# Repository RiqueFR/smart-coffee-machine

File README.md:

# smart-coffee-machine

Esse projeto consiste na adaptação de uma cafeteira comum, em uma cafeteira smart, usando um microcontrolador ESP32, sensores e conexão com o [Home Assistant](https://www.home-assistant.io/), por meio do sistema [ESPHome](https://esphome.io/),
que permite a automatização dela com outros dispositivos, como por exemplo a Alexa.</br>
É possível assistir a demonstração e explicação do projeto por meio do seguinte vídeo:

Esse projeto usa as ferramentas/plataformas:
- PlatformIO
- Home Assistant
- ESPHome
- Node-RED
- Alexa

## Features

- Escolher a quantidade de café por meio do número de xícaras
- Interface na cafeteira (botões para escolher a quantidade de xícaras, display para exibir a quantidade e o status)
- Conexão com o Home Assistant
- Por meio da conexão com o Home Assistant é possível integrar a cafeteira com diversos outro serviços, como por exemplo comandos de voz da Alexa
- Enchimento automático do reservatório de água da cafeteira
- Sensor para não ser ativada sem uma xícara

## Usage

Para usar esse projeto, você precisa de pelo menos o ESPHome instalado, para que seja possível passar o código para o microcontrolador, basta colocar o projeto na pasta do ESPHome, e usar as ferramentas da plataforma para subir o código.</br>
Existe a versão do código na branch "main" que não necessita do ESPHome, porém ela é desprovida de qualquer conexão com o Home Assistant ou Alexa.</br>

O projeto foi feito com o intuito de ser apresentado na amostra de projetos da disciplina de Projeto Integrado de Computação 2 da UFES, portanto alguns detalhes foram pensados para isso, e caso venha a ser reproduzido para uso pessoal, devem ser abordados outros métodos.</br>
Portanto, até existe um esquemático do projeto na branch "schematic", mas ele deve ser alterado para o seu uso, e apenas usado como base.</br>

O projeto foi calibrado para uso com a cafeteira que tínhamos acesso, portanto ele deve ser recalibrado para outras cafeteiras, isso pode ser feito colocando xícaras de café cheias de água no reservatório da cafeteira e observar as diferenças de distância lidas pelo sensor de ultrassom para cada xícara,
esse valor deve ser setado na variável apropriada.</br>

Para apresentar o projeto na amostra, foi usado uma pequena bomba de água para encher o reservatório, o que não é prático caso o projeto seja feito para uso, o melhor seria usar uma válvula que libera ou bloqueia a passagem de água, e que esteja ligada a tubulação,
para que o enchimento seja feito de maneira totalmente automática.</br>

A branch configs possui configurações das conexões/ferrantas usadas pelo projeto, arquivos de configuração do Home Assistant, Node-RED e ESPHome. Os arquivos de configuração do ESPHome estão desatualizados, o arquivo correto de configuração é o que está
presente nesta branch, o "esp32.yaml".

## TO-DO

- Melhorar documentação
- Modularizar mais o código para que as configurações possam ser feitas na interface do ESPHome (como número de xícaras)
- Criar um modo de calibração, para que seja possível usar com todas cafeteiras
- Criar um esquemático geral, que seja fácil de ser reproduzido para todos os projetos.

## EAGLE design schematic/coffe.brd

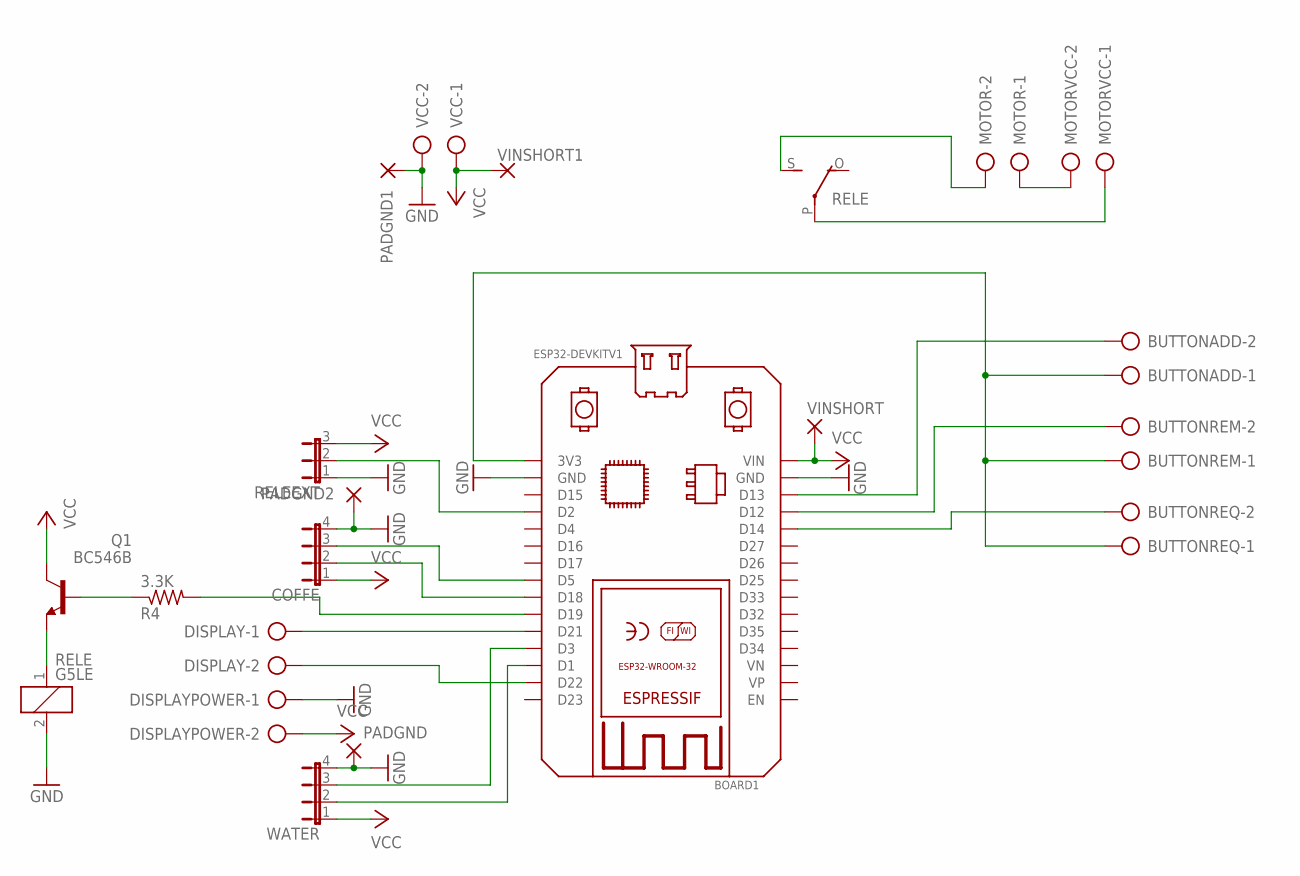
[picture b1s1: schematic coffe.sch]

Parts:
BOARD1: ESP32DEVKITV1; ESP32-DEVKITV1
BUTTONADD: AK500/2-H
BUTTONREM: AK500/2-H
BUTTONREQ: AK500/2-H
COFFE: JP4E; JP4
DISPLAY: AK500/2-H
DISPLAYPOWER: AK500/2-H
MOTOR: AK500/2-H
MOTORVCC: AK500/2-H
PADGND, PADGND1, PADGND2: 2,15/1,0
Q1: BC546B; TO92-EBC
R4: 3.3K; 0204/7
RELE: G5LE
RELEEXT: JP2E; JP2
VCC: AK500/2-H
VINSHORT, VINSHORT1: 2,15/1,0
WATER: JP4E; JP4

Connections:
GND: BOARD1.GND, BOARD1.GND@1 (GND), COFFE.4, DISPLAYPOWER.1, PADGND.1, PADGND1.1, PADGND2.1, RELE.2, RELEEXT.1, VCC.2, WATER.4
unnamed: BOARD1.D3, WATER.3
unnamed: BOARD1.D1, WATER.2
unnamed: BOARD1.D5, COFFE.3
unnamed: BOARD1.D18, COFFE.2
unnamed: BOARD1.D14, BUTTONREQ.2
unnamed: BOARD1.D19, R4.2
unnamed: BOARD1.3V3, BUTTONADD.1, BUTTONREM.1, BUTTONREQ.1
unnamed: BOARD1.D22, DISPLAY.2
unnamed: Q1.B, R4.1
unnamed: Q1.E, RELE.1
unnamed: MOTOR.2, RELE.S
unnamed: MOTOR.1, MOTORVCC.2
unnamed: MOTORVCC.1, RELE.P
unnamed: BOARD1.D2, RELEEXT.2
unnamed: BOARD1.D13, BUTTONADD.2
unnamed: BOARD1.D21, DISPLAY.1
unnamed: BOARD1.D12, BUTTONREM.2
VCC: BOARD1.VIN, COFFE.1, DISPLAYPOWER.2, Q1.C, RELEEXT.3, VCC.1, VINSHORT.1, VINSHORT1.1, WATER.1

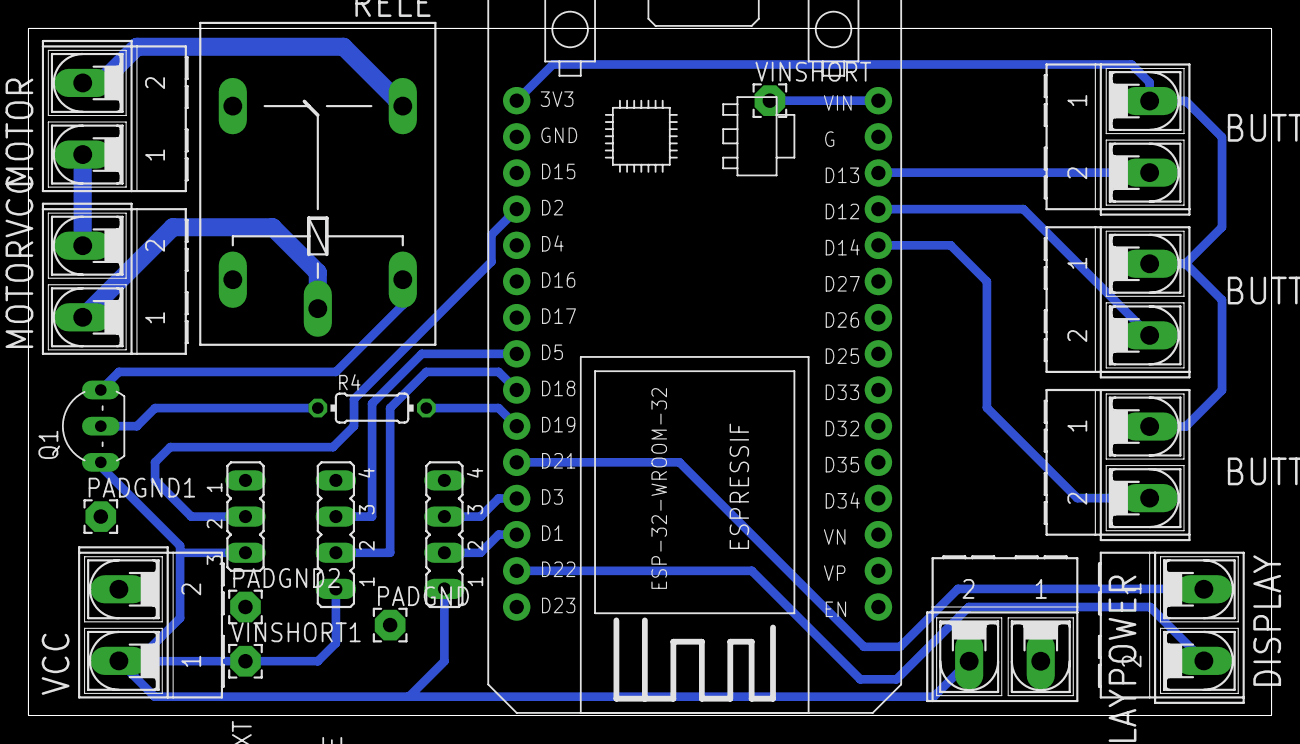
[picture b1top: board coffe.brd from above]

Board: 2 copper layers, 87.3 x 48.2 mm, 20 parts (0 on the bottom side), 19 nets.

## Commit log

2022-05-10 add .gitignore
2022-05-10 Created new Cup detection library and tested Switch
2022-05-12 integrando tem xícara com quantidad de água, e lendo botões
2022-05-14 consertando main.c
2022-05-14 ignorando .vscode/extensions.json
2022-05-14 consertando a biblioteca button
2022-05-18 Integrando componentes
2022-05-19 integracao funcionando
2022-06-02 Add schematic files
2022-06-02 New pinout for the copper board
2022-06-02 New Updated schematic, need some fix
2022-06-02 New schematic design, should make it better
2022-06-03 Routing complete
2022-06-07 Added display information to the coffee machine
2022-06-07 Change coffee machine code to a class, to prepare to adapt it for ESPHome syntax
2022-06-30 clean the repository
2022-06-30 Move libs out
2022-06-30 Moved button code to .h, to use with esphome
2022-06-30 Moved cup code to .h, to use with esphome
2022-06-30 Moved ultrasonic code to .h, to use with esphome
2022-06-30 Moved coffee code to .h, to use with esphome
2022-06-30 moved codes to principal directory
2022-07-04 Limpando branch
2022-07-04 configurações
2022-07-05 adicionado checagem de conexao e limite de reservatorio para desligar a cafeteira
2022-07-05 Changed button pins to constant values, change hasCup to a attribute, changed code to only check cups when coffee is requested
2022-07-05 Rename class Button to remove conflicts with ESPHome Button class
2022-07-05 Change 'coffee' code to use states to check water fill and drain
2022-07-12 Board revision and File to print
2022-07-28 add esphome yaml
2022-07-28 new configs
2022-07-29 Set pins as schematics
2022-08-05 Changed buttons pin, fix relays
2023-05-22 Tune coffe machine
